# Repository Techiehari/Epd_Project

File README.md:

# Epd_Project: 3.3V to 15V Boost Converter

## Overview
This repository contains the KiCad design files for a custom DC-to-DC power converter. The circuit is designed to take a 3.3V input and provide a regulated 15V output at 1A, using the MP3429 IC.

## Key Specifications
* **Input Voltage:** 3.3V
* **Output Voltage:** 15V
* **Output Current:** 1A
* **Core IC:** MPS MP3429

## Tools Used
* **EDA Software:** KiCad
* **Custom Footprints/Symbols:** Designed specifically for the MP3429 and associated components.

## Repository Structure
* `/Custom_libraries` - Contains project-specific library files.
* `/models` - 3D models for PCB visualization.
* `/MP3429_Custom.pretty` - Custom footprint library for the MP3429 IC.
* `/symbols` - Custom schematic symbols.
* `Bom.csv` - Bill of Materials containing component selection and costs.
* `Epd_Project.kicad_sch` - The main KiCad schematic file.
* `Epd_Project.kicad_pcb` - The main KiCad PCB layout file.

## Design Details
Detailed design equations, component selection justifications, and technical specifications derived from the MP3429 datasheet are maintained in the project report documents.

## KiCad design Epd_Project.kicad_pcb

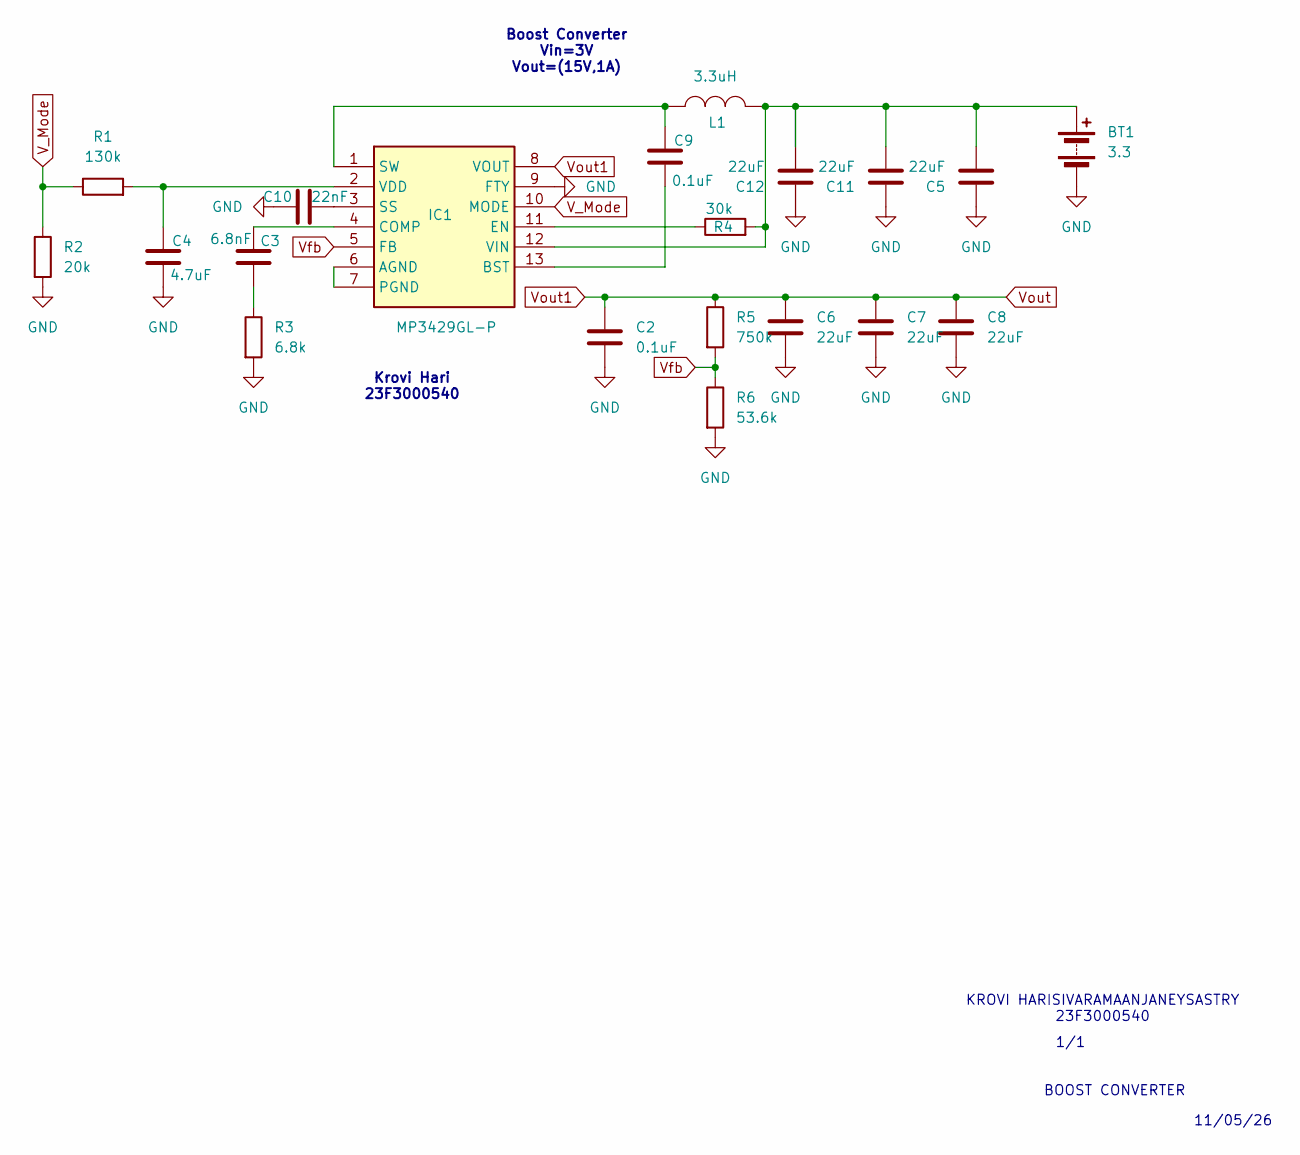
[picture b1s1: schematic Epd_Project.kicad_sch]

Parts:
BT1: 3.3; TerminalBlock_Phoenix_PT-1,5-2-5.0-H_1x02_P5.00mm_Horizontal
C2, C9: 0.1uF; C_0805_2012Metric
C3: 6.8nF; C_0805_2012Metric
C4: 4.7uF; C_0805_2012Metric
C5, C6, C7, C8, C11, C12: 22uF; C_1206_3216Metric
C10: 22nF; C_0805_2012Metric
IC1: MP3429GL-P; MP3429GLP; Mouser Part Number 946-MP3429GL-P
L1: 3.3uH; L_7.3x7.3_H4.5
R1: 130k; R_0805_2012Metric
R2: 20k; R_0805_2012Metric
R3: 6.8k; R_0805_2012Metric
R4: 30k; R_0805_2012Metric
R5: 750k; R_0805_2012Metric
R6: 53.6k; R_0805_2012Metric

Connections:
GND: BT1.2 (-), C2.2, C4.2, C5.1, C6.2, C7.2, C8.2, C10.1, C11.1, C12.1, IC1.9 (FTY), R2.2, R3.2, R6.2
unnamed: BT1.1 (+), C5.2, C11.2, C12.2, IC1.12 (VIN), L1.2 (T2), R4.2
unnamed: C3.2, R3.1
unnamed: IC1.6 (AGND), IC1.7 (PGND)
unnamed: C9.2, IC1.13 (BST)
unnamed: C3.1, IC1.4 (COMP)
unnamed: IC1.11 (EN), R4.1
unnamed: C10.2, IC1.3 (SS)
unnamed: C9.1, IC1.1 (SW), L1.1 (T1)
unnamed: C4.1, IC1.2 (VDD), R1.2
V_Mode: IC1.10 (MODE), R1.1, R2.1
Vfb: IC1.5 (FB), R5.2, R6.1
Vout: C2.1, C6.1, C7.1, C8.1, IC1.8 (VOUT), R5.1

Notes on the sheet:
Boost Converter Vin=3V Vout=(15V,1A)
KROVI HARISIVARAMAANJANEYSASTRY 23F3000540
11/05/26
BOOST CONVERTER
Krovi Hari 23F3000540
1/1

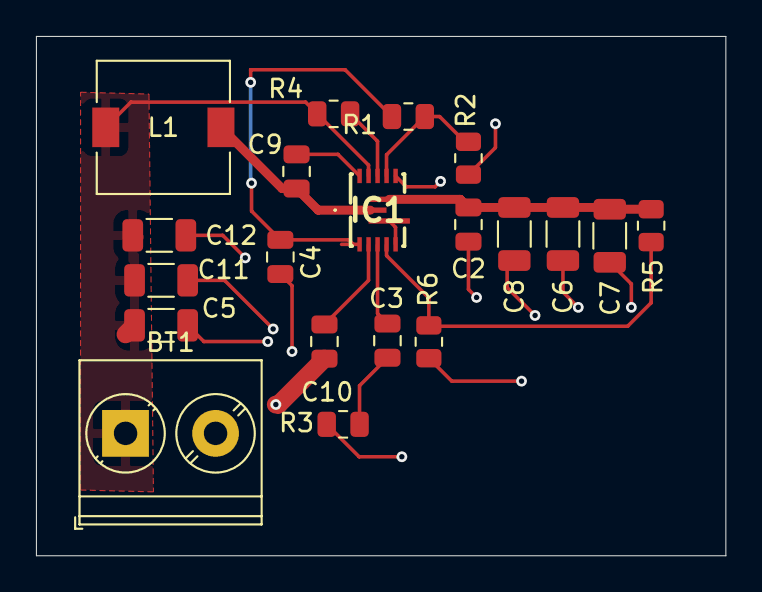
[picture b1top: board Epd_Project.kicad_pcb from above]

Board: 2 copper layers, 38.3 x 28.9 mm, 20 parts (0 on the bottom side), 13 nets.

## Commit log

2026-05-13 Initial commit of Epd_Project
2026-05-13 Add project README with specifications
2026-05-13 Clarify output regulation in README
    Updated the description to clarify the output regulation method.
